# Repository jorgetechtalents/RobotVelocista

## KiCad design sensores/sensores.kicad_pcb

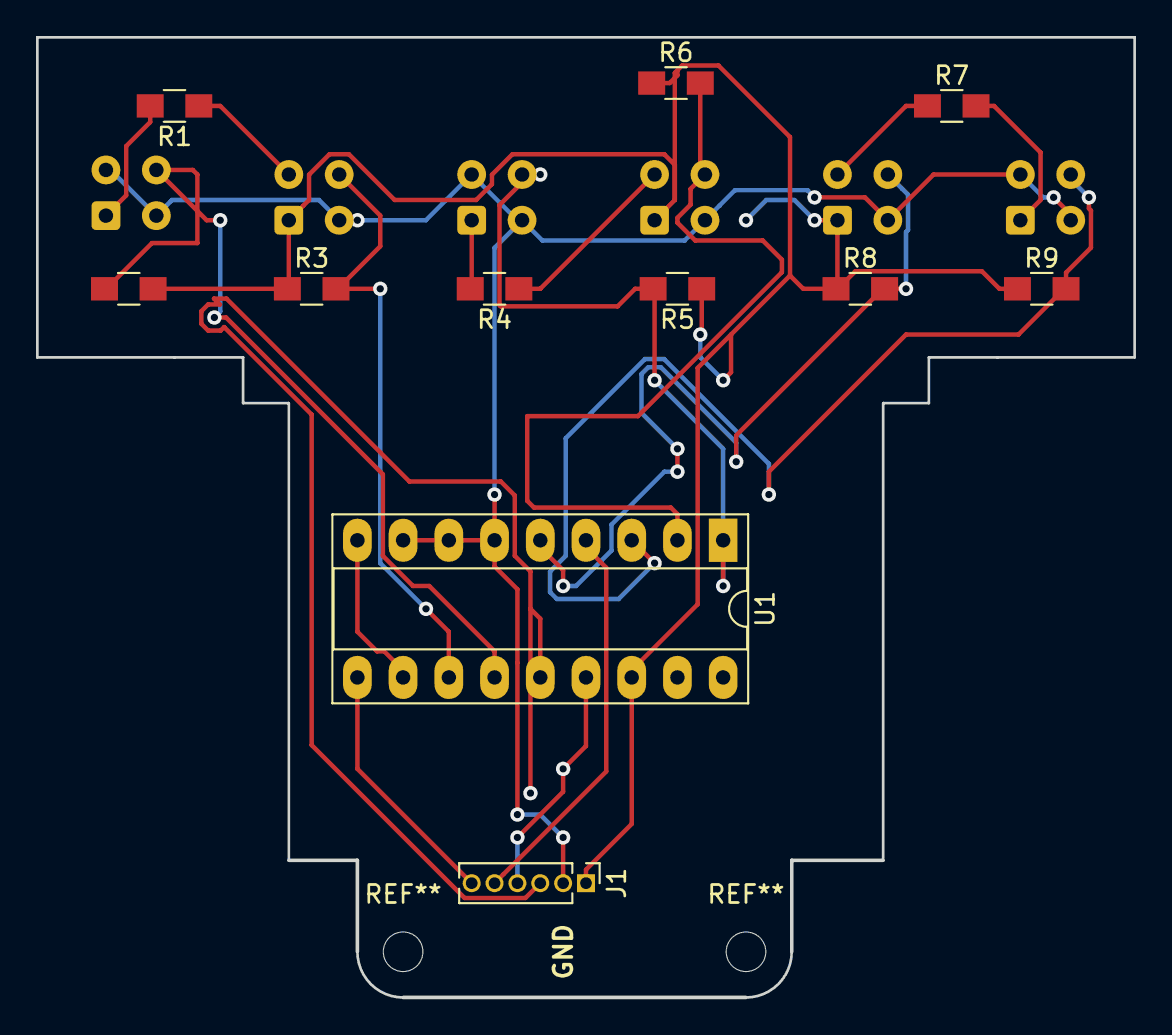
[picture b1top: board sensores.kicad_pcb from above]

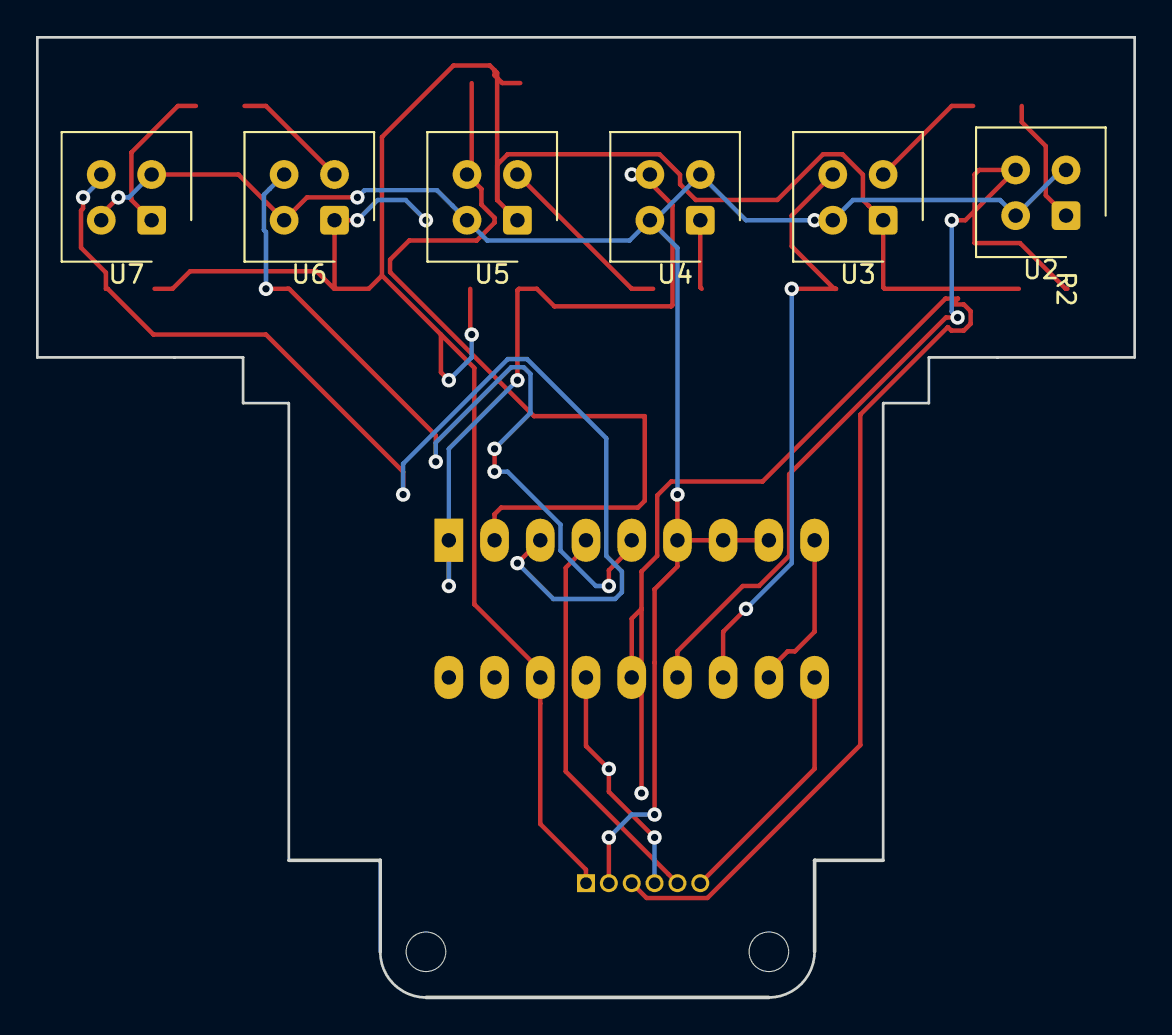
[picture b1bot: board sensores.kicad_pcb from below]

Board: 2 copper layers, 60.9 x 53.3 mm, 17 parts (6 on the bottom side), 19 nets.

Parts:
J1: Conn_01x06_Female; Pin_Header_Straight_1x06_Pitch1.27mm
R1, R4, R7: 82k; R_0805_HandSoldering
R2, R3, R5, R6, R8, R9: 10k; R_0805_HandSoldering
U1: 4053; DIP-18_W7.62mm_Socket_LongPads
U2, U3, U4, U5, U6, U7: CNY70; Vishay_CNY70

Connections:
+5V: J1.1, R2.1, R3.1, R5.1, R6.1, R8.1, R9.1, U1.16, U3.1, U5.1, U6.1
/linea1: J1.3, U1.14
/linea2: J1.4, U1.15
/linea3: J1.5, U1.4
/linea_selec: J1.6, U1.10
/sensor1: R3.2, U1.12, U3.3
/sensor2: R2.2, U1.13, U2.3
/sensor3: R6.2, U1.2, U5.3
/sensor4: R5.2, U1.1, U4.3
/sensor5: R8.2, U1.5, U6.3
/sensor6: R9.2, U1.3, U7.3
GND: J1.2, U1.6, U1.7, U1.8, U2.2, U2.4, U3.4, U4.2, U4.4, U5.4, U6.4, U7.2, U7.4
unnamed: R1.1, U3.2
unnamed: R1.2, U2.1
unnamed: R4.1, U5.2
unnamed: R4.2, U4.1
unnamed: R7.1, U6.2
unnamed: R7.2, U7.1
unnamed: U1.9, U1.11
